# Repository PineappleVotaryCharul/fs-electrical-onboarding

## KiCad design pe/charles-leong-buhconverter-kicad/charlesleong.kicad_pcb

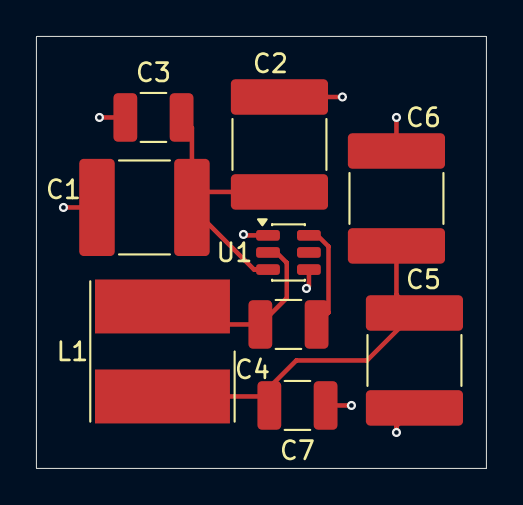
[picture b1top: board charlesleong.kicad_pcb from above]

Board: 2 copper layers, 25.0 x 24.0 mm, 9 parts (0 on the bottom side), 5 nets.

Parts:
C1, C2, C5, C6: 10μf; C_2220_5750Metric_Pad1.97x5.40mm_HandSolder
C3, C4, C7: 100nF; C_1210_3225Metric_Pad1.33x2.70mm_HandSolder
L1: 12 µH; L_Wurth_WE-PD2SR-7850
U1: TPS542025DDCR; SOT-23-6

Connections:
+5V: C5.1, C6.1, C7.1, L1.2
+15V: C1.1, C2.1, C3.1, U1.3 (VIN)
GND: C1.2, C2.2, C3.2, C5.2, C6.2, C7.2, U1.1 (GND), U1.4 (FB)
unnamed: C4.1, U1.6 (BOOT)
unnamed: C4.2, L1.1, U1.2 (SW)
